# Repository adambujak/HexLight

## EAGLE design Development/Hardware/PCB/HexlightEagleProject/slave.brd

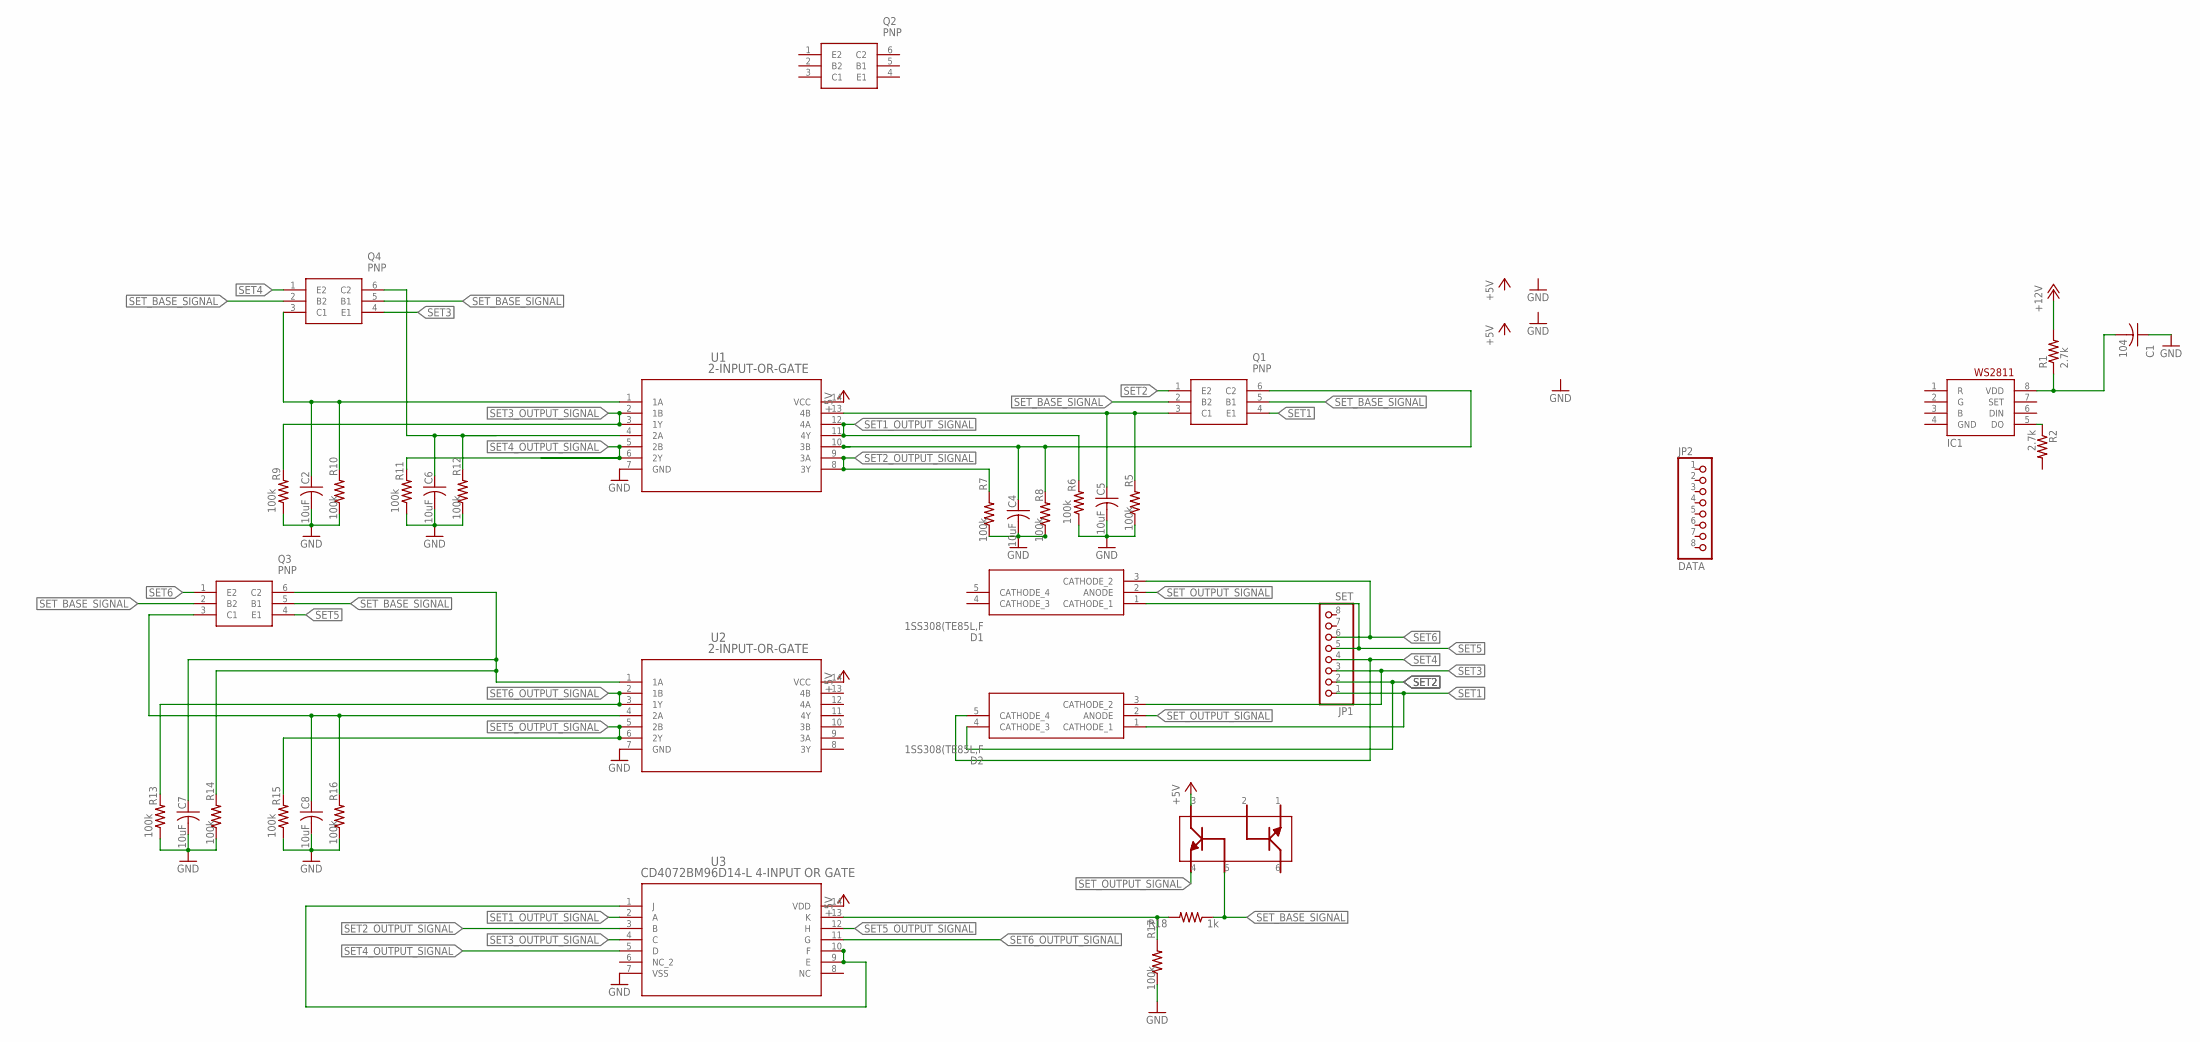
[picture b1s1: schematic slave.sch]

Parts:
C1: 104; C0805
C2, C4, C5, C6, C7, C8: 10uF; C0805
D1, D2: 1SS308(TE85L,F; SOT95P275X130-5N
IC1: WS2811-SOP8; SO08-SKINNYPADS
JP1: SET; 1X08-3.5MM
JP2: DATA; 1X08-3.5MM
Q1, Q2, Q3, Q4: PNP; SOT65P210X110-6N
R1, R2: 2.7k; M0805
R5, R6, R7, R8, R9, R10, R11, R12, R13, R14, R15, R16, R17: 100k; M0805
R18: 1k; M0805
U1, U2: 2-INPUT-OR-GATE; D14-L
U3: CD4072BM96D14-L 4-INPUT OR GATE; D14-L
U$1: MBT3904DW1T1G; SOT236

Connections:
+5V: U1.14 (VCC), U2.14 (VCC), U3.14 (VDD), U$1.3
+12V: R1.2
GND: C1.1, C2.2, C4.2, C5.2, C6.2, C7.2, C8.2, IC1.4 (GND), R5.1, R6.1, R7.1, R8.1, R9.1, R10.1, R11.1, R12.1, R13.1, R14.1, R15.1, R16.1, R17.1, U1.7 (GND), U2.7 (GND), U3.7 (VSS)
unnamed: IC1.5 (DO), R2.1
unnamed: C1.2, IC1.8 (VDD), R1.1
unnamed: C5.1, Q1.3 (C1), R5.2, U1.13 (4B)
unnamed: U3.1 (J), U3.9 (E), U3.10 (F)
unnamed: Q4.6 (C2), R12.2, U1.4 (2A)
unnamed: C4.1, Q1.6 (C2), R8.2, U1.10 (3B)
unnamed: C2.1, Q4.3 (C1), R10.2, U1.1 (1A)
unnamed: R17.2, R18.2, U3.13 (K)
unnamed: C7.1, Q3.6 (C2), R14.2, U2.1 (1A)
unnamed: C8.1, Q3.3 (C1), R16.2, U2.4 (2A)
SET1: D2.1 (CATHODE_1), JP1.1, Q1.4 (E1)
SET1_OUTPUT_SIGNAL: R6.2, U1.11 (4Y), U1.12 (4A), U3.2 (A)
SET2: D2.4 (CATHODE_3), JP1.2, Q1.1 (E2)
SET2_OUTPUT_SIGNAL: R7.2, U1.8 (3Y), U1.9 (3A), U3.3 (B)
SET3: D2.3 (CATHODE_2), JP1.3, Q4.4 (E1)
SET3_OUTPUT_SIGNAL: R9.2, U1.2 (1B), U1.3 (1Y), U3.4 (C)
SET4: D2.5 (CATHODE_4), JP1.4, Q4.1 (E2)
SET4_OUTPUT_SIGNAL: R11.2, U1.5 (2B), U1.6 (2Y), U3.5 (D)
SET5: D1.1 (CATHODE_1), JP1.5, Q3.4 (E1)
SET5_OUTPUT_SIGNAL: R15.2, U2.5 (2B), U2.6 (2Y), U3.12 (H)
SET6: D1.3 (CATHODE_2), JP1.6, Q3.1 (E2)
SET6_OUTPUT_SIGNAL: R13.2, U2.2 (1B), U2.3 (1Y), U3.11 (G)
SET_BASE_SIGNAL: Q1.2 (B2), Q1.5 (B1), Q3.2 (B2), Q3.5 (B1), Q4.2 (B2), Q4.5 (B1), R18.1, U$1.5
SET_OUTPUT_SIGNAL: D1.2 (ANODE), D2.2 (ANODE), U$1.4

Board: 2 copper layers, 36 parts (0 on the bottom side), 26 nets, no tracks yet.

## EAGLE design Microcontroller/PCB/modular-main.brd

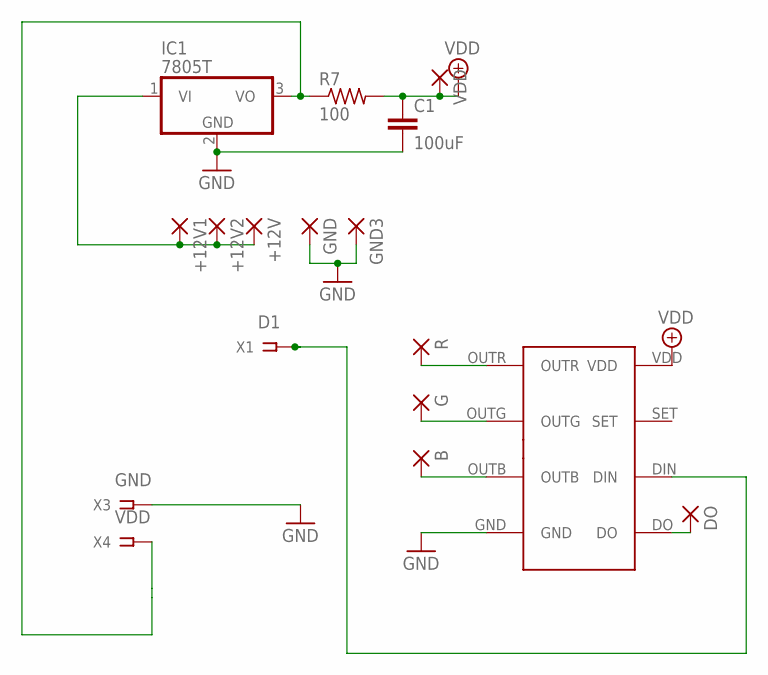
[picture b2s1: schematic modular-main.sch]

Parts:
0: WS2811; SOP8
+12V, +12V1, +12V2: SMD5; SMD2,54-5,08
B: SMD5; SMD2,54-5,08
C1: 100uF; C0805
DO: SMD5; SMD2,54-5,08
G: SMD5; SMD2,54-5,08
GND, GND3: SMD5; SMD2,54-5,08
IC1: 7805T; TO220H
R: SMD5; SMD2,54-5,08
R7: 100; R0805
VDD: SMD5; SMD2,54-5,08
X1: D1; SSW-101-02-G-S
X3: GND; SSW-101-02-G-S
X4: VDD; SSW-101-02-G-S

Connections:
+5V: 0.VDD, C1.1, R7.2, VDD.1
GND: 0.GND, C1.2, GND.1, GND3.1, IC1.2 (GND), X3.1
unnamed: 0.DIN, X1.1
unnamed: 0.DO, DO.1
unnamed: 0.OUTB, B.1
unnamed: 0.OUTG, G.1
unnamed: 0.OUTR, R.1
unnamed: IC1.3 (VO), R7.1, X4.1
unnamed: +12V.1, +12V1.1, +12V2.1, IC1.1 (VI)

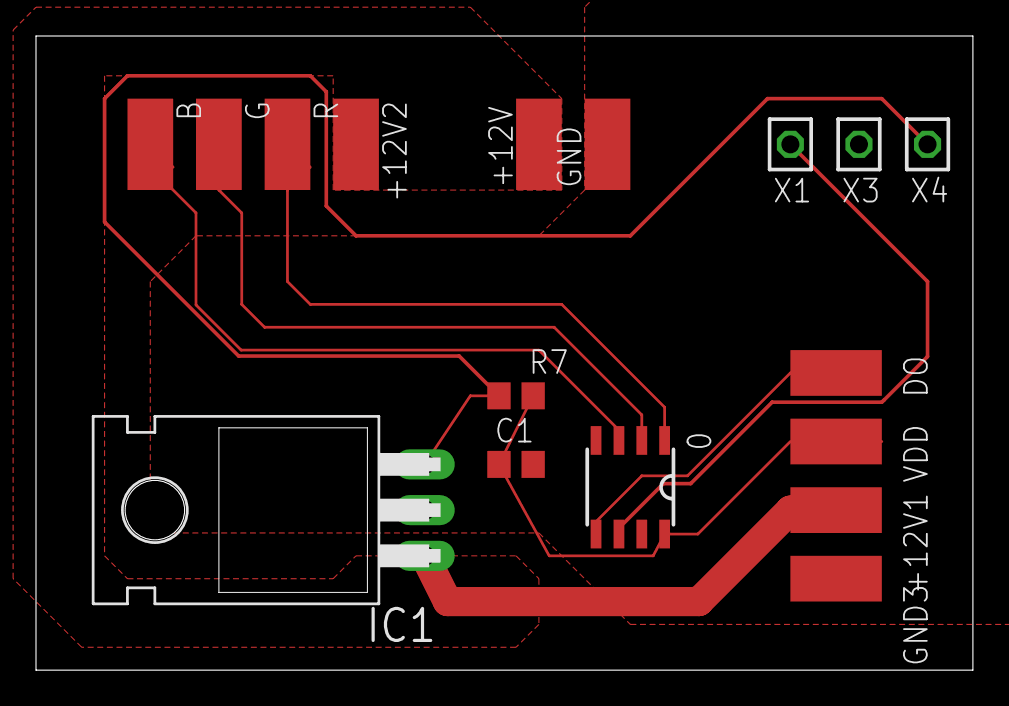
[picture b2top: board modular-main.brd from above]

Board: 2 copper layers, 52.0 x 35.2 mm, 17 parts (0 on the bottom side), 9 nets.

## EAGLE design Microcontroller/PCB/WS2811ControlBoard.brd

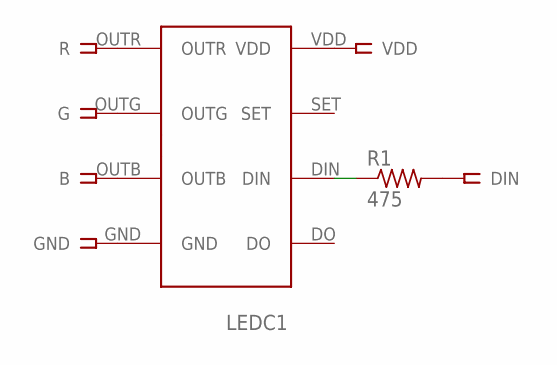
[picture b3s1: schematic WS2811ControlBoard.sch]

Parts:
B: SSW-101-02-G-S
DIN: SSW-101-02-G-S
G: SSW-101-02-G-S
GND: SSW-101-02-G-S
LEDC1: WS2811; SOP8
R: SSW-101-02-G-S
R1: 475; R0805W
VDD: SSW-101-02-G-S

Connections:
unnamed: LEDC1.OUTR, R.1
unnamed: G.1, LEDC1.OUTG
unnamed: B.1, LEDC1.OUTB
unnamed: GND.1, LEDC1.GND
unnamed: LEDC1.VDD, VDD.1
unnamed: DIN.1, R1.2
unnamed: LEDC1.DIN, R1.1

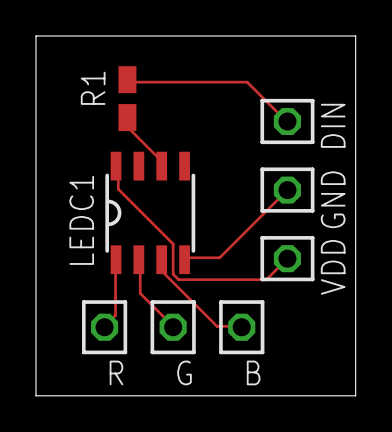
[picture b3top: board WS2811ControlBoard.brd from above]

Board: 2 copper layers, 17.8 x 20.0 mm, 8 parts (0 on the bottom side), 7 nets.

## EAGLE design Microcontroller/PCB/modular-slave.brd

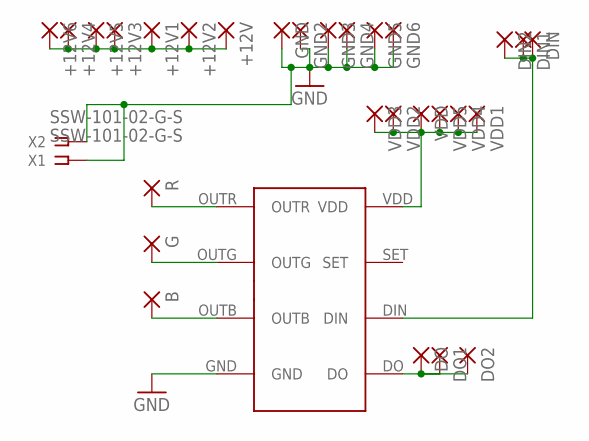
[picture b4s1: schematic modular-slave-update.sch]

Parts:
0: WS2811; SOP8
+12V, +12V1, +12V2, +12V3, +12V4, +12V5, +12V6: SMD5; SMD2,54-5,08
B: SMD5; SMD2,54-5,08
DIN, DIN1, DIN2: SMD5; SMD2,54-5,08
DO, DO1, DO2: SMD5; SMD2,54-5,08
G: SMD5; SMD2,54-5,08
GND, GND2, GND3, GND4, GND5, GND6: SMD5; SMD2,54-5,08
R: SMD5; SMD2,54-5,08
VDD, VDD1, VDD2, VDD3, VDD4, VDD5: SMD5; SMD2,54-5,08
X1, X2: SSW-101-02-G-S

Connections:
GND: 0.GND, GND.1, GND2.1, GND3.1, GND4.1, GND5.1, GND6.1, X1.1, X2.1
unnamed: 0.DO, DO.1, DO1.1, DO2.1
unnamed: 0.OUTB, B.1
unnamed: 0.OUTG, G.1
unnamed: 0.OUTR, R.1
unnamed: +12V.1, +12V1.1, +12V2.1, +12V3.1, +12V4.1, +12V5.1, +12V6.1
unnamed: 0.VDD, VDD.1, VDD1.1, VDD2.1, VDD3.1, VDD4.1, VDD5.1
unnamed: 0.DIN, DIN.1, DIN1.1, DIN2.1

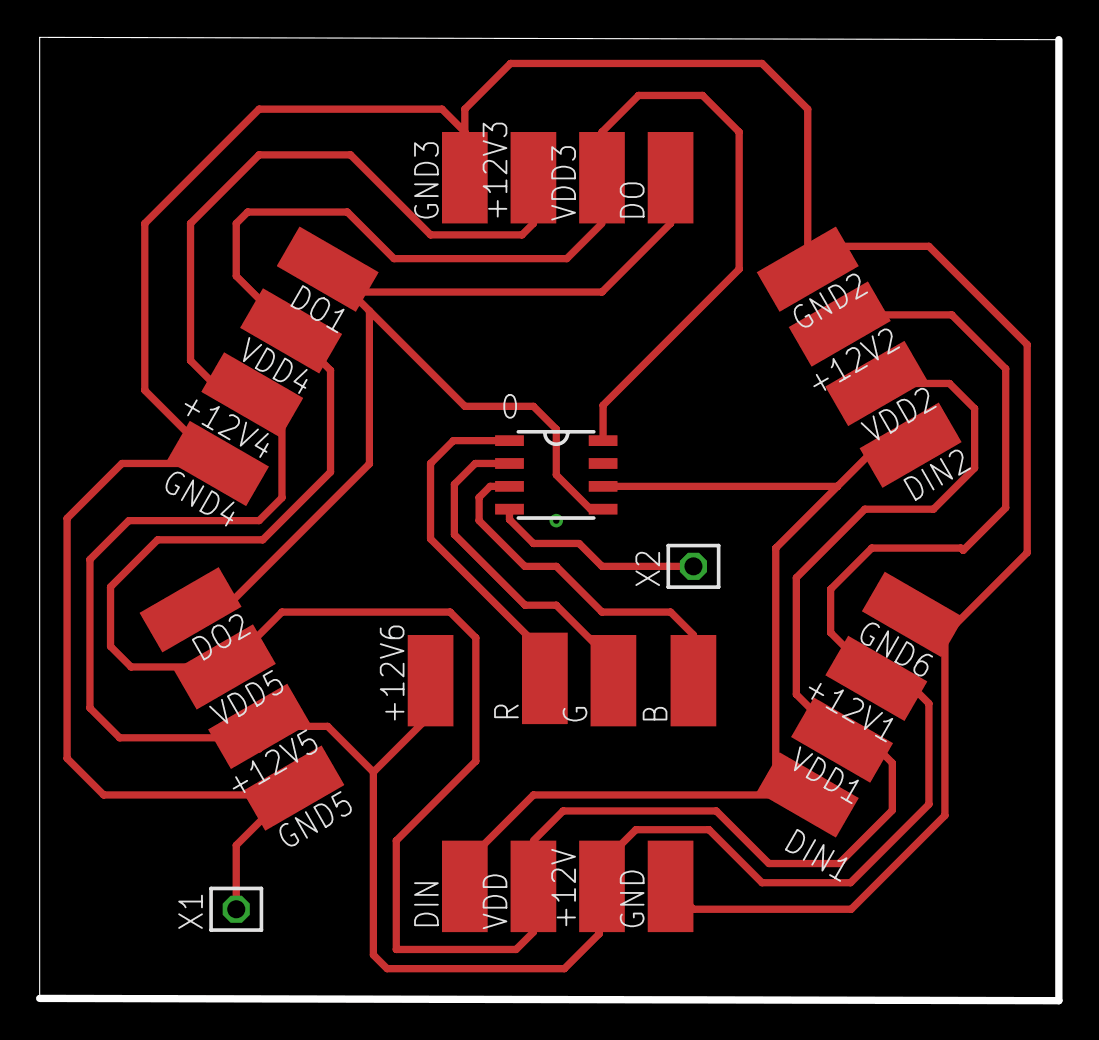
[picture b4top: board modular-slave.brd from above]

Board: 2 copper layers, 56.6 x 53.4 mm, 31 parts (0 on the bottom side), 8 nets.

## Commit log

2018-11-17 initial commit of app
2018-11-17 initial commit of nodemcu code
2019-01-05 updated schematic
2019-02-18 cleaned up android code
2019-02-18 Fixed 200 ok error, and cleaned android code
2019-02-18 cleaned up micro code and made it much more efficient and modular
2019-02-18 Added brightness changing function to micro and android
2019-02-18 fixed brightness bug
2019-02-18 changed to stroud and added pin 4 - make sure to test 4
2019-02-26 added wifi device name
2019-02-26 app changed to have a global string for url, and led array fixed for micro
2019-02-28 added icon and renamed app
2019-03-09 updated app
2019-03-09 added new boards for modular design
2019-03-09 added animations to nodemcu
2019-03-09 changed code to proper method using only one pin for LED control
2019-03-09 added CAD model
2019-03-09 Added pulse and random twinkle animation
2019-03-09 Added MARKII PCB designs
2019-03-09 Fixed issue where app wasn't toggling correct panel
2019-09-24 fixed hexagon alignment issue
2019-09-25 restructured repo directory layout and added resource folder
2019-09-25 started input and output mixing circuit
2019-09-25 added mux and voltage regulator datasheets
2019-09-25 Started Eagle schematic for slave
2019-09-25 adding animations
2019-09-26 New CAD for HexLight
2019-09-26 finished example circuit for input/output mixing
2019-09-26 finished example circuit for input/output mixing - recommit
2019-09-26 Connected DIN and DO since it's really just DATA[i]
2019-09-26 finished input and output switching portion of schematic
2019-10-04 started working on new app
2019-10-05 hexagon adding done
2019-10-05 Further work on mixing circuit
2019-10-17 Continued designing CAD Model
2019-10-24 Changed design to three screw holes
